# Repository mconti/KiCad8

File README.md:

# KiCad8
Esempi di disegno KiCad

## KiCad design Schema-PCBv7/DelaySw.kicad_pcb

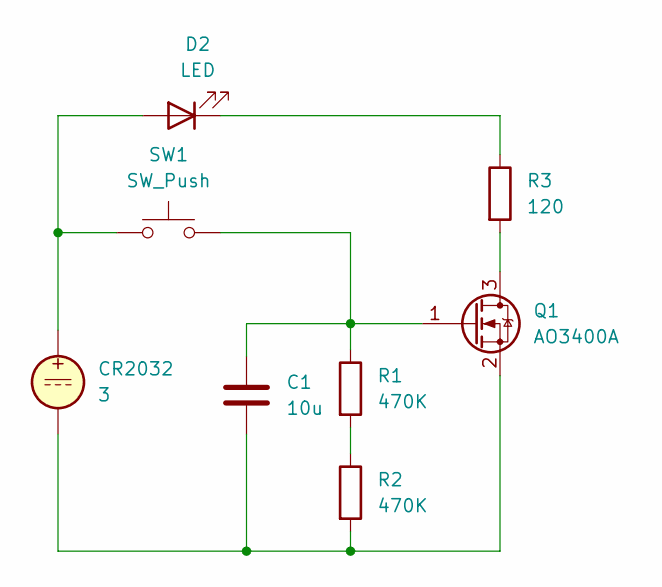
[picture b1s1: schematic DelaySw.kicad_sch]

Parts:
C1: 10u; C_0805_2012Metric; LCSC C15850
CR2032: 3; BatteryHolder_Keystone_3009_1x2450; LCSC C70380
D2: LED; LED_PLCC_2835; LCSC C516126
Q1: AO3400A; SOT-23; LCSC C91104
R1, R2: 470K; R_0805_2012Metric; LCSC C17709
R3: 120; R_1206_3216Metric; LCSC C17909
SW1: SW_Push; SW_Push_1P1T_XKB_TS-1187A; LCSC C318884

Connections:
unnamed: CR2032.1, D2.2 (A), SW1.1
unnamed: D2.1 (K), R3.1
unnamed: Q1.3 (D), R3.2
unnamed: C1.1, Q1.1 (G), R1.1, SW1.2
unnamed: C1.2, CR2032.2, Q1.2 (S), R2.2
unnamed: R1.2, R2.1

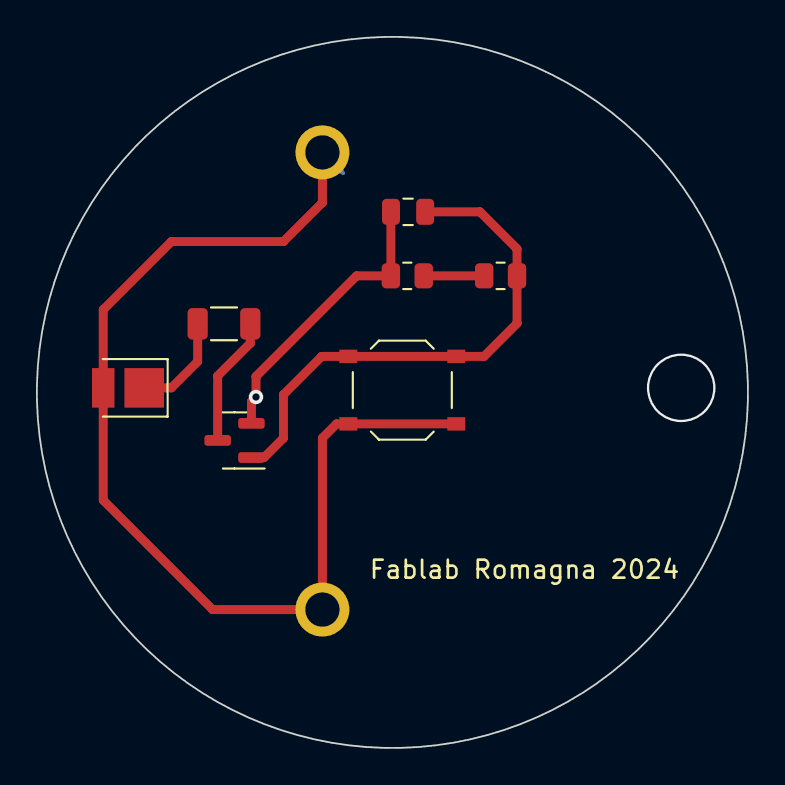
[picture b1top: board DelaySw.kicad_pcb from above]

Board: 2 copper layers, 39.5 x 39.5 mm, 8 parts (1 on the bottom side), 6 nets.

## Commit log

2024-03-09 Primo commit
